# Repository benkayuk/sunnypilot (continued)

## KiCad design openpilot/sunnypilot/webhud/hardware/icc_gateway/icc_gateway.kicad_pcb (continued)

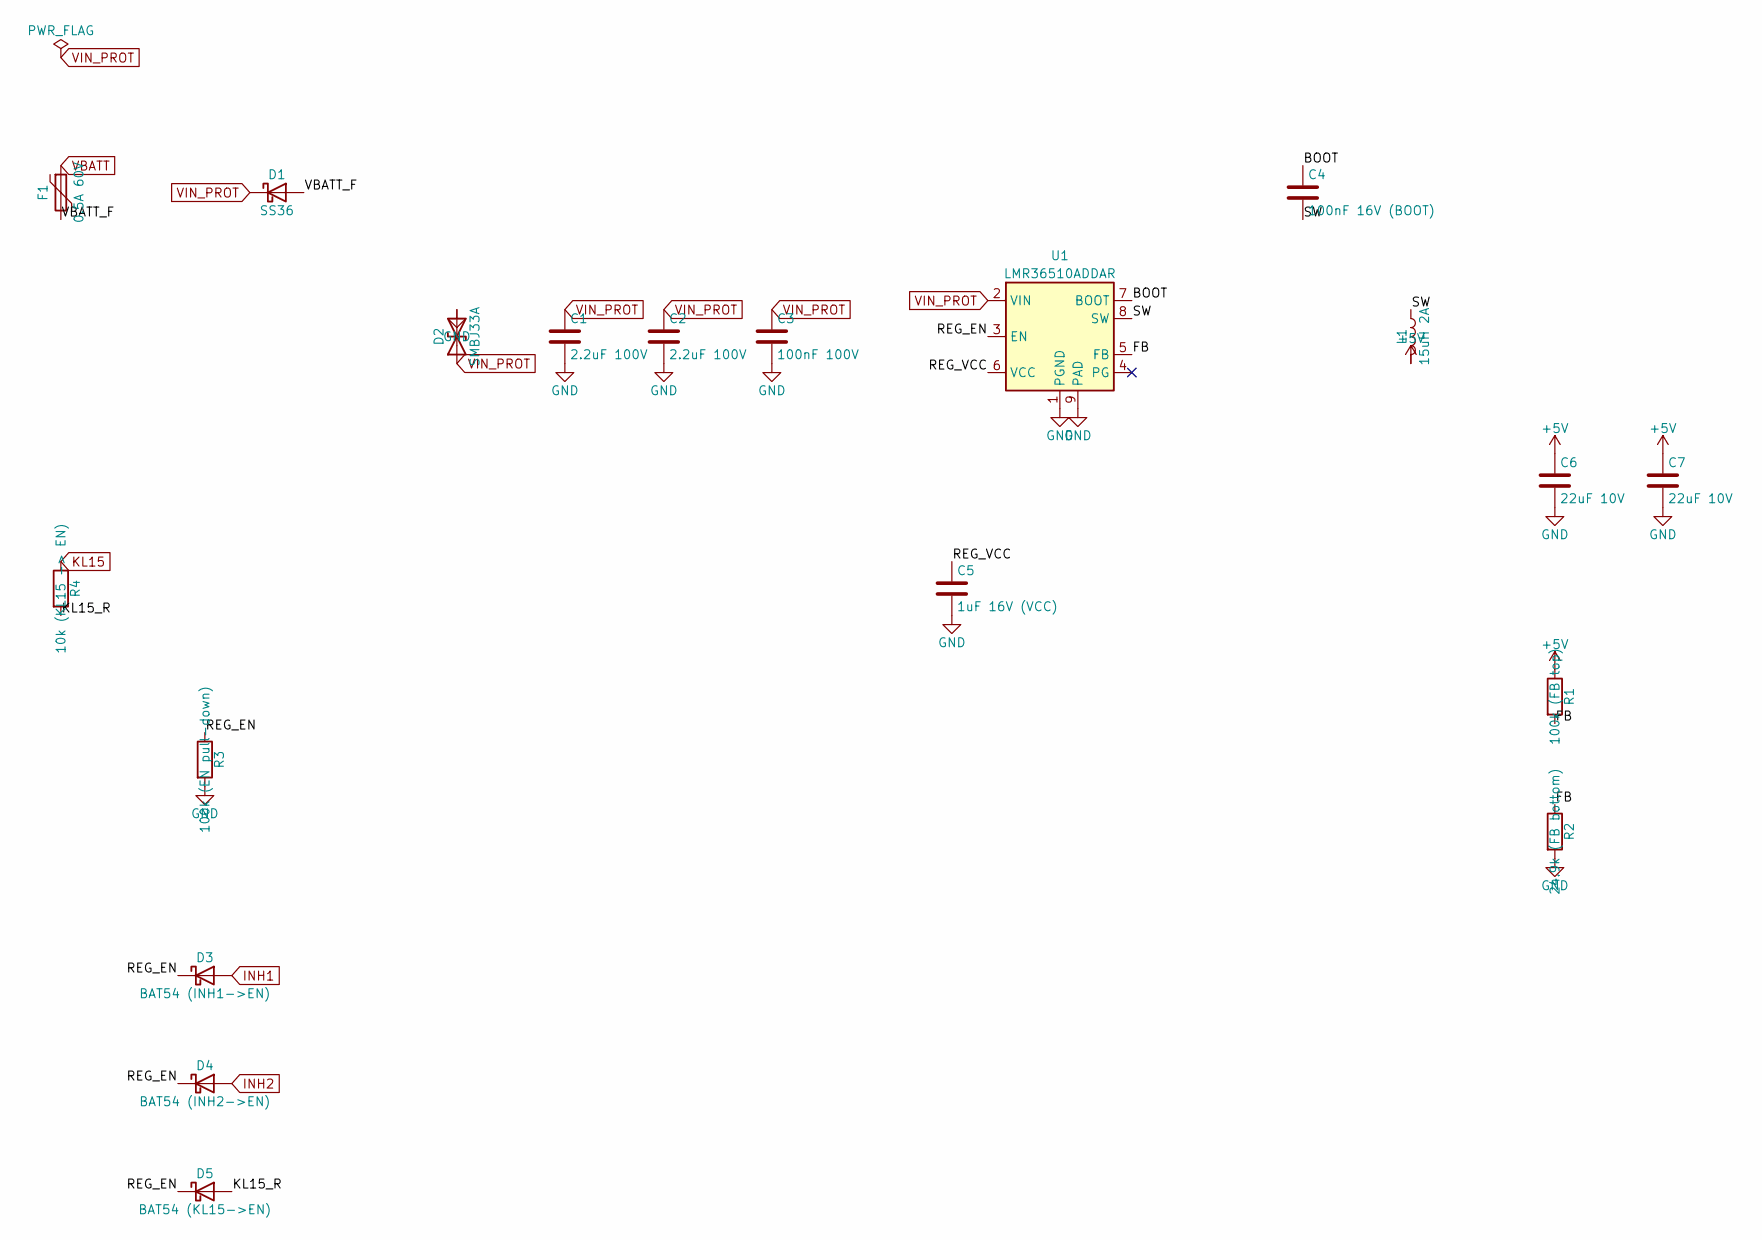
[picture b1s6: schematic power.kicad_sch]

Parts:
C1, C2: 2.2uF 100V; C_1210_3225Metric
C3: 100nF 100V; C_0805_2012Metric
C4: 100nF 16V (BOOT); C_0603_1608Metric
C5: 1uF 16V (VCC); C_0603_1608Metric
C6, C7: 22uF 10V; C_0805_2012Metric
D1: SS36; D_SMA
D2: SMBJ33A; D_SMB
D3: BAT54 (INH1->EN); D_SOD-123
D4: BAT54 (INH2->EN); D_SOD-123
D5: BAT54 (KL15->EN); D_SOD-123
F1: 0.5A 60V; Fuse_1812_4532Metric
L1: 15uH 2A; L_Bourns_SRN6045TA
R1: 100k (FB top); R_0805_2012Metric
R2: 24.9k (FB bottom); R_0805_2012Metric
R3: 100k (EN pull-down); R_0805_2012Metric
R4: 10k (KL15 -> EN); R_0805_2012Metric
U1: LMR36510ADDAR; Texas_HTSOP-8-1EP_3.9x4.9mm_P1.27mm_EP2.95x4.9mm_Mask2.4x3.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

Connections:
+5V: C6.1, C7.1, L1.2, R1.1; also elsewhere on the board
/Power/BOOT: C4.1, U1.7 (BOOT)
/Power/FB: R1.2, R2.1, U1.5 (FB)
/Power/KL15_R: D5.2 (A), R4.2
/Power/REG_EN: D3.1 (K), D4.1 (K), D5.1 (K), R3.1, U1.3 (EN)
/Power/REG_VCC: C5.1, U1.6 (VCC)
/Power/SW: C4.2, L1.1, U1.8 (SW)
/Power/VBATT_F: D1.2 (A), F1.2
GND: C1.2, C2.2, C3.2, C5.2, C6.2, C7.2, D2.2 (A2), R2.2, R3.2, U1.1 (PGND), U1.9 (PAD); also elsewhere on the board
INH1: D3.2 (A); also elsewhere on the board
INH2: D4.2 (A); also elsewhere on the board
KL15: R4.1; also elsewhere on the board
VBATT: F1.1; also elsewhere on the board
VIN_PROT: C1.1, C2.1, C3.1, D1.1 (K), D2.1 (A1), U1.2 (VIN); also elsewhere on the board

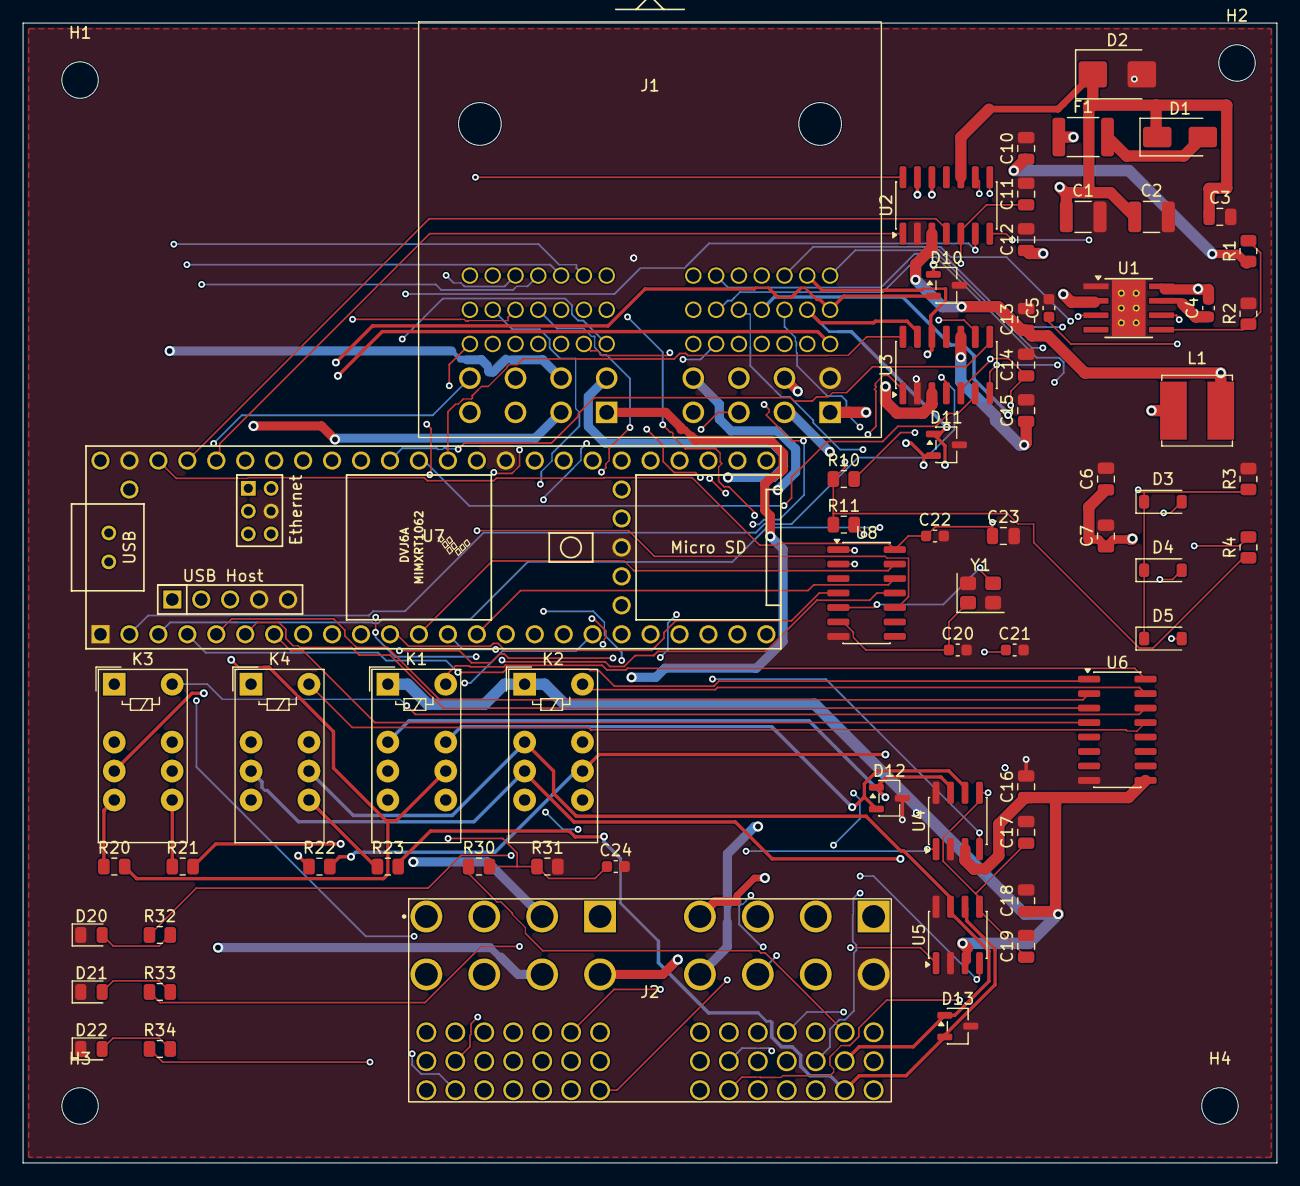
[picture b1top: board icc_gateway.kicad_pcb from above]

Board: 4 copper layers, 110.0 x 100.0 mm, 70 parts (0 on the bottom side), 116 nets.

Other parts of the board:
H1, H2, H3, H4: MountingHole_3.2mm_M3

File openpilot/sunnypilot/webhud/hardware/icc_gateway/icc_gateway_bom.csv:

"Reference","Value","Footprint","QUANTITY"
"BT1","CR2032 (RTC)","Battery:BatteryHolder_Keystone_3034_1x20mm","1"
"C1,C2","2.2uF 100V","Capacitor_SMD:C_1210_3225Metric","2"
"C3","100nF 100V","Capacitor_SMD:C_0805_2012Metric","1"
"C4","100nF 16V (BOOT)","Capacitor_SMD:C_0603_1608Metric","1"
"C5","1uF 16V (VCC)","Capacitor_SMD:C_0603_1608Metric","1"
"C6,C7","22uF 10V","Capacitor_SMD:C_0805_2012Metric","2"
"C10","100nF (U2 VCC)","Capacitor_SMD:C_0805_2012Metric","1"
"C11","100nF (U2 VIO)","Capacitor_SMD:C_0805_2012Metric","1"
"C12","100nF (U2 VBAT)","Capacitor_SMD:C_0805_2012Metric","1"
"C13","100nF (U3 VCC)","Capacitor_SMD:C_0805_2012Metric","1"
"C14","100nF (U3 VIO)","Capacitor_SMD:C_0805_2012Metric","1"
"C15","100nF (U3 VBAT)","Capacitor_SMD:C_0805_2012Metric","1"
"C16","100nF (U4 VCC)","Capacitor_SMD:C_0805_2012Metric","1"
"C17","100nF (U4 VIO)","Capacitor_SMD:C_0805_2012Metric","1"
"C18","100nF (U5 VCC)","Capacitor_SMD:C_0805_2012Metric","1"
"C19","100nF (U5 VIO)","Capacitor_SMD:C_0805_2012Metric","1"
"C20,C21","15pF","Capacitor_SMD:C_0603_1608Metric","2"
"C22","100nF (U8 VDD)","Capacitor_SMD:C_0603_1608Metric","1"
"C23","10uF (U8 VDD)","Capacitor_SMD:C_0805_2012Metric","1"
"C24","10nF (KL15 sense)","Capacitor_SMD:C_0603_1608Metric","1"
"D1","SS36","Diode_SMD:D_SMA","1"
"D2","SMBJ33A","Diode_SMD:D_SMB","1"
"D3","BAT54 (INH1->EN)","Diode_SMD:D_SOD-123","1"
"D4","BAT54 (INH2->EN)","Diode_SMD:D_SOD-123","1"
"D5","BAT54 (KL15->EN)","Diode_SMD:D_SOD-123","1"
"D10","NUP2105L (car IBUS1 ESD)","Package_TO_SOT_SMD:SOT-23-3","1"
"D11","NUP2105L (car IBUS2 ESD)","Package_TO_SOT_SMD:SOT-23-3","1"
"D12","NUP2105L (ICC IBUS1 ESD)","Package_TO_SOT_SMD:SOT-23-3","1"
"D13","NUP2105L (ICC IBUS2 ESD)","Package_TO_SOT_SMD:SOT-23-3","1"
"D20","LED green (ACTIVE)","LED_SMD:LED_0805_2012Metric","1"
"D21","LED yellow (CAR bus)","LED_SMD:LED_0805_2012Metric","1"
"D22","LED blue (ICC bus)","LED_SMD:LED_0805_2012Metric","1"
"F1","0.5A 60V","Fuse:Fuse_1812_4532Metric","1"
"J1,J2","160013-0641","icc_gateway:Molex_stAK50h_160013-0641","2"
"K1","G6S-2 DC5 (bridge IBUS1)","Relay_THT:Relay_DPDT_Omron_G6S-2","1"
"K2","G6S-2 DC5 (bridge IBUS2)","Relay_THT:Relay_DPDT_Omron_G6S-2","1"
"K3","G6S-2 DC5 (terminators IBUS1)","Relay_THT:Relay_DPDT_Omron_G6S-2","1"
"K4","G6S-2 DC5 (terminators IBUS2)","Relay_THT:Relay_DPDT_Omron_G6S-2","1"
"L1","15uH 2A","Inductor_SMD:L_Bourns_SRN6045TA","1"
"R1","100k (FB top)","Resistor_SMD:R_0805_2012Metric","1"
"R2","24.9k (FB bottom)","Resistor_SMD:R_0805_2012Metric","1"
"R3","100k (EN pull-down)","Resistor_SMD:R_0805_2012Metric","1"
"R4","10k (KL15 -> EN)","Resistor_SMD:R_0805_2012Metric","1"
"R10","10k (KL15 -> U2 WAKE)","Resistor_SMD:R_0805_2012Metric","1"
"R11","10k (KL15 -> U3 WAKE)","Resistor_SMD:R_0805_2012Metric","1"
"R20","120R (car IBUS1 term)","Resistor_SMD:R_0805_2012Metric","1"
"R21","120R (ICC IBUS1 term)","Resistor_SMD:R_0805_2012Metric","1"
"R22","120R (car IBUS2 term)","Resistor_SMD:R_0805_2012Metric","1"
"R23","120R (ICC IBUS2 term)","Resistor_SMD:R_0805_2012Metric","1"
"R30","100k (KL15 sense)","Resistor_SMD:R_0805_2012Metric","1"
"R31","22k (KL15 sense)","Resistor_SMD:R_0805_2012Metric","1"
"R32-R34","1k","Resistor_SMD:R_0805_2012Metric","3"
"U1","LMR36510ADDAR","Package_SO:Texas_HTSOP-8-1EP_3.9x4.9mm_P1.27mm_EP2.95x4.9mm_Mask2.4x3.1mm_ThermalVias","1"
"U2","TJA1043T/1 (car IBUS1)","Package_SO:SOIC-14_3.9x8.7mm_P1.27mm","1"
"U3","TJA1043T/1 (car IBUS2)","Package_SO:SOIC-14_3.9x8.7mm_P1.27mm","1"
"U4","TJA1051T/3 (ICC IBUS1)","Package_SO:SOIC-8_3.9x4.9mm_P1.27mm","1"
"U5","TJA1051T/3 (ICC IBUS2)","Package_SO:SOIC-8_3.9x4.9mm_P1.27mm","1"
"U6","ULN2003A","Package_SO:SOIC-16_3.9x9.9mm_P1.27mm","1"
"U7","Teensy 4.1","teensy:Teensy41","1"
"U8","MCP2518FD-E/SL","Package_SO:SOIC-14_3.9x8.7mm_P1.27mm","1"
"Y1","20MHz 3225","Crystal:Crystal_SMD_3225-4Pin_3.2x2.5mm","1"
"J3,J4","Female header 1x24 2.54 mm (Teensy sockets)","Connector_PinSocket_2.54mm:PinSocket_1x24_P2.54mm_Vertical","2"
"J2 pigtail","Molex 160014-0014 + 160014-0011 receptacles with crimped leads, or salvaged ICC harness stub","(wire)","1"

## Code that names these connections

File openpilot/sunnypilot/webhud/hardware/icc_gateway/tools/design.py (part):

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    1: ("p", "GND"), 34: ("p", "GND"), 47: ("p", "GND"), 52: ("p", "GND"), 58: ("p", "GND"), 59: ("p", "GND"), 64: ("p", "GND"),
    48: ("p", "+5V"), 46: ("p", "+3V3"),   # 15/51 are the same 3V3 rail: left unconnected (NC) so ERC sees one driver
    50: ("l", "VBAT_RTC"),
    44: ("g", "CAN1_TX"), 45: ("g", "CAN1_RX"),     # pins 22/23
    3: ("g", "CAN2_TX"), 2: ("g", "CAN2_RX"),       # pins 1/0
    23: ("g", "CAN3_TX"), 22: ("g", "CAN3_RX"),     # pins 31/30
    13: ("g", "SPI_MOSI"), 14: ("g", "SPI_MISO"), 35: ("g", "SPI_SCK"), 12: ("g", "CAN4_CS"), 11: ("g", "CAN4_INT"),  # 11/12/13/10/9
    4: ("g", "RLY1"), 5: ("g", "RLY2"), 6: ("g", "RLY3"), 7: ("g", "RLY4"),   # pins 2..5
    8: ("g", "CAR1_STBN"), 9: ("g", "CAR1_EN"), 10: ("g", "CAR1_ERRN"),        # pins 6,7,8
    36: ("g", "CAR2_STBN"), 37: ("g", "CAR2_EN"), 38: ("g", "CAR2_ERRN"),      # pins 14,15,16
    39: ("l", "KL15_SENSE"),                                                  # pin 17 / A3
    16: ("l", "LED1"), 17: ("l", "LED2"), 18: ("l", "LED3"),                   # pins 24,25,26
}
for n in range(1, 68):
    if n in T:
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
